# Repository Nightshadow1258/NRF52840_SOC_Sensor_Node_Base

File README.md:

# NRF52840 SOC Sensor Node Base Board

# Version
release Version will be tracked by branches.
Each Version that is/will be produced will branch of main.
Main will always be the most recent version.

## V2.00
- Base Board for the [NRF52840_SOC](https://github.com/Nightshadow1258/NRF52840_SOC)
- changed connector to one with additional retention tabs to increase stability.

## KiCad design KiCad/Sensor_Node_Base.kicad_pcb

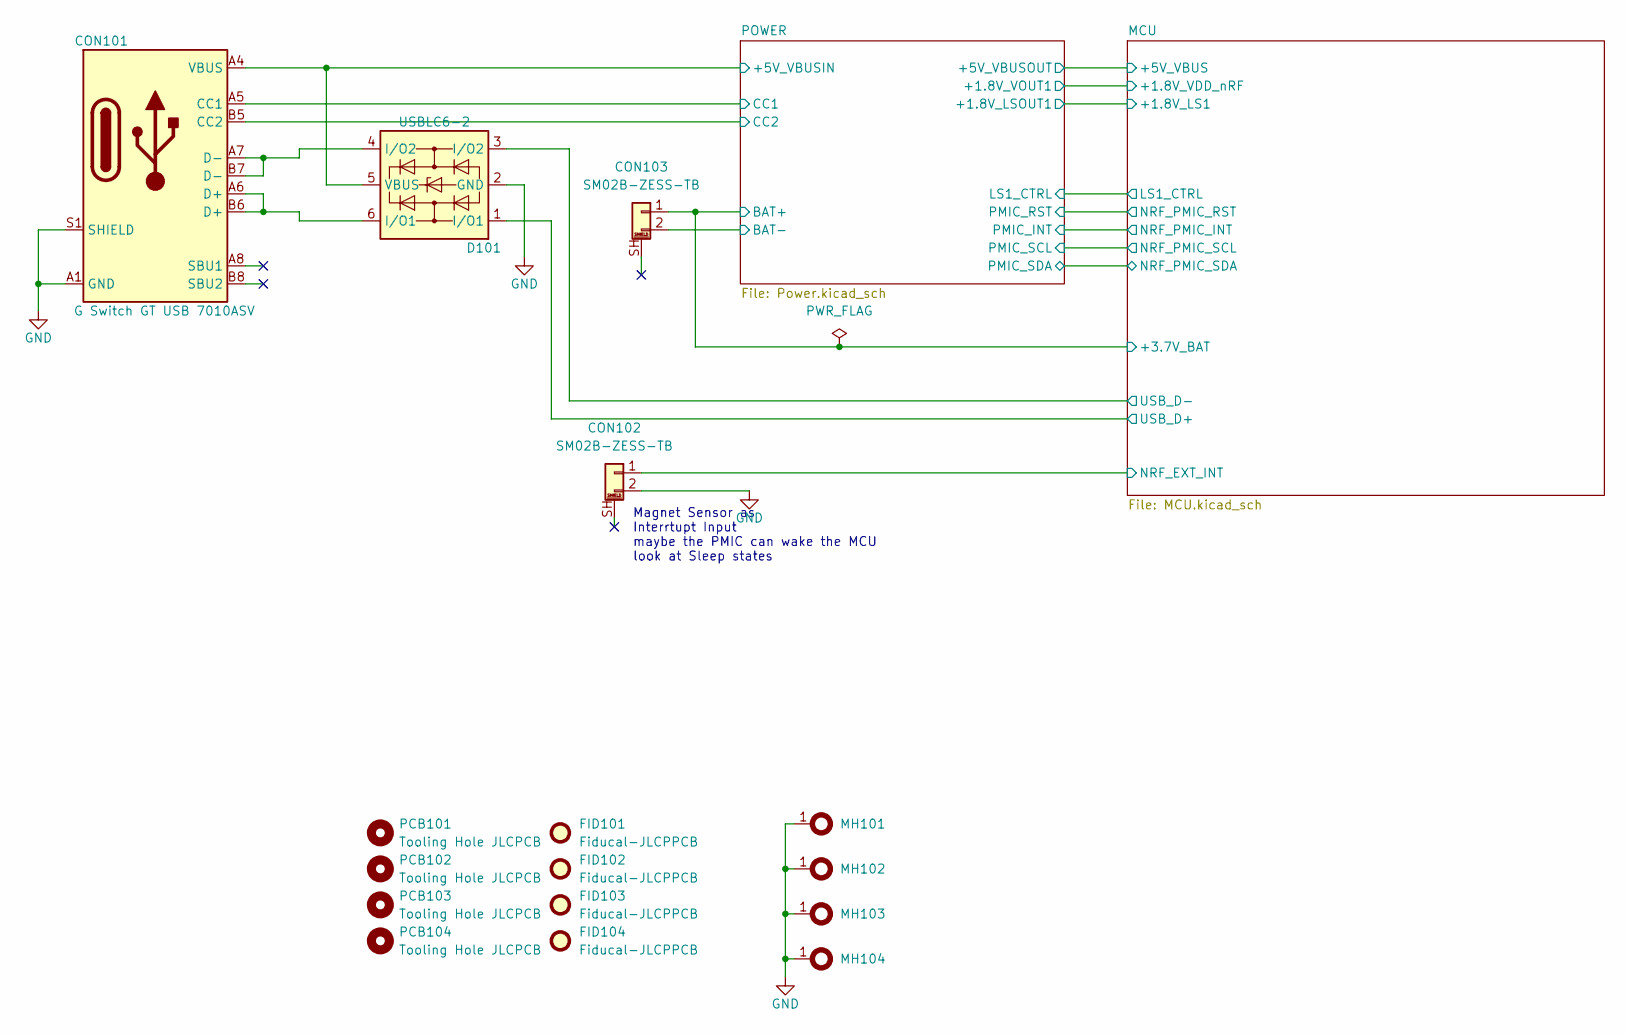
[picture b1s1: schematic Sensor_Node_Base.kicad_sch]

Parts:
CON101: G Switch GT USB 7010ASV; CON-GEN-USB_C-16P; LCSC Part # C2988369
CON102, CON103: SM02B-ZESS-TB; CON-SM02B-ZESS_TB
D101: USBLC6-2; SOT-23-6; LCSC Part # C7519
FID101, FID102, FID103, FID104: Fiducal-JLCPPCB; PCB-FID-JLCPCB
MH101, MH102, MH103, MH104: MountingHole_2.5mm_Pad_Via
PCB101, PCB102, PCB103, PCB104: Tooling Hole JLCPCB; PCB-NPTH-JLCPCB

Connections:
/MCU/+3.7V_BAT: CON103.1; also elsewhere on the board
/MCU/NRF_EXT_INT: CON102.1; also elsewhere on the board
/MCU/USB_D+: D101.1 (I/O1); also elsewhere on the board
/MCU/USB_D-: D101.3 (I/O2); also elsewhere on the board
/POWER/+5V_VBUSIN: CON101.A4 (VBUS), CON101.A9 (VBUS), CON101.B4 (VBUS), CON101.B9 (VBUS), D101.5 (VBUS); also elsewhere on the board
/POWER/BAT-: CON103.2; also elsewhere on the board
/POWER/CC1: CON101.A5 (CC1); also elsewhere on the board
/POWER/CC2: CON101.B5 (CC2); also elsewhere on the board
GND: CON101.A1 (GND), CON101.A12 (GND), CON101.B1 (GND), CON101.B12 (GND), CON101.S1 (SHIELD), CON102.2, D101.2 (GND), MH101.1, MH102.1, MH103.1, MH104.1; also elsewhere on the board
unnamed: CON101.A6 (D+), CON101.B6 (D+), D101.6 (I/O1)
unnamed: CON101.A7 (D-), CON101.B7 (D-), D101.4 (I/O2)

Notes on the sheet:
Magnet Sensor as Interrtupt Input maybe the PMIC can wake the MCU look at Sleep states

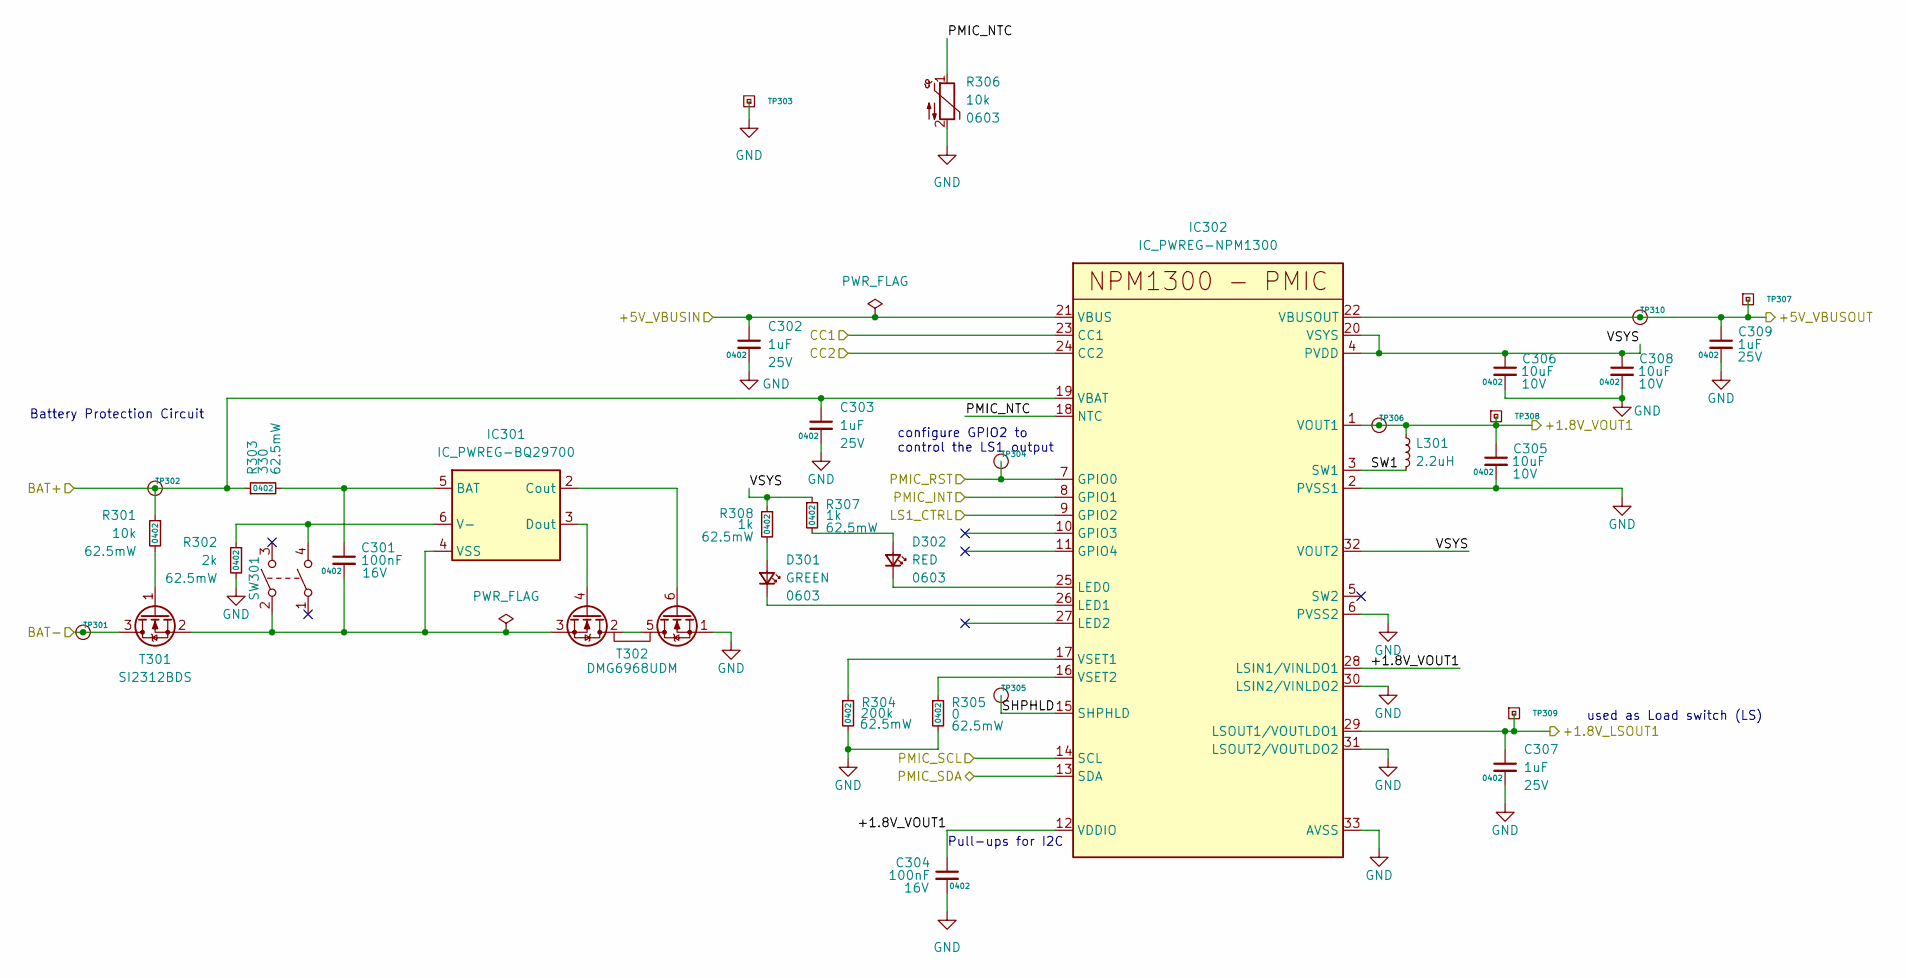
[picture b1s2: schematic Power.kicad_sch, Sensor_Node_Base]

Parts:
C301, C304: 100nF; C_0402_1005Metric; Voltage 16V; LCSC Part # C1525
C302, C303, C307, C309: 1uF; C_0402_1005Metric; Voltage 25V; LCSC Part # C52923
C305, C306, C308: 10uF; C_0603_1608Metric; Voltage 10V; LCSC Part # C96446
D301: GREEN; D_0603_1608Metric; LCSC Part # C84267
D302: RED; D_0603_1608Metric; LCSC Part # C2286
IC301: IC_PWREG-BQ29700; WSON-6_1.5x1.5mm_P0.5mm; LCSC Part # C183096
IC302: IC_PWREG-NPM1300; QFN-32-1EP_5x5mm_P0.5mm_EP3.6x3.6mm_ThermalVias
L301: 2.2uH; L_0806; LCSC Part # C2838367
R301: 10k; R_0402_1005Metric; Power Rating 62.5mW; LCSC Part # C25744
R302: 2k; R_0402_1005Metric; Power Rating 62.5mW; LCSC Part # C4109
R303: 330; R_0402_1005Metric; Power Rating 62.5mW; LCSC Part # C25104
R304: 200k; R_0402_1005Metric; Power Rating 62.5mW; LCSC Part # C25764
R305: 0; R_0402_1005Metric; Power Rating 62.5mW; LCSC Part # C17168
R306: 10k; R_0603_1608Metric; LCSC Part # C142556
R307, R308: 1k; R_0402_1005Metric; Power Rating 62.5mW; LCSC Part # C11702
SW301: SW-GEN-TS-1187A; SW-PUSH-DPST-XKS-TS-1187A; LCSC Part # C318884
T301: SI2312BDS; SOT-23; LCSC Part # C351405
T302: DMG6968UDM; SOT-23-6; LCSC Part # C2762931
TP301, TP302, TP304, TP305, TP306, TP310: TP; TP_Pad_D0.9mm
TP303, TP307, TP308, TP309: Testpoint-BASE; TP_THT_D0.8mm

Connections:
/MCU/+1.8V_LS1: C307.1, IC302.29 (LSOUT1/VOUTLDO1), TP309.1; also elsewhere on the board
/MCU/+1.8V_VDD_nRF: C304.1, C305.1, IC302.1 (VOUT1), IC302.12 (VDDIO), IC302.28 (LSIN1/VINLDO1), L301.1, TP306.1, TP308.1; also elsewhere on the board
/MCU/+3.7V_BAT: C303.1, IC302.19 (VBAT), R301.1, R303.1, TP302.1; also elsewhere on the board
/MCU/+5V_VBUS: C309.1, IC302.22 (VBUSOUT), TP307.1, TP310.1; also elsewhere on the board
/MCU/LS1_CTRL: IC302.9 (GPIO2); also elsewhere on the board
/MCU/NRF_PMIC_INT: IC302.8 (GPIO1); also elsewhere on the board
/MCU/NRF_PMIC_RST: IC302.7 (GPIO0), TP304.1; also elsewhere on the board
/MCU/NRF_PMIC_SCL: IC302.14 (SCL); also elsewhere on the board
/MCU/NRF_PMIC_SDA: IC302.13 (SDA); also elsewhere on the board
/POWER/+5V_VBUSIN: C302.1, IC302.21 (VBUS); also elsewhere on the board
/POWER/BAT-: T301.3 (D), TP301.1; also elsewhere on the board
/POWER/CC1: IC302.23 (CC1); also elsewhere on the board
/POWER/CC2: IC302.24 (CC2); also elsewhere on the board
/POWER/PMIC_NTC: IC302.18 (NTC), R306.1
/POWER/SHPHLD: IC302.15 (SHPHLD), TP305.1
/POWER/SW1: IC302.3 (SW1), L301.2
/POWER/VSYS: C306.1, C308.1, IC302.4 (PVDD), IC302.20 (VSYS), IC302.32 (VOUT2), R307.1, R308.1
GND: C302.2, C303.2, C304.2, C305.2, C306.2, C307.2, C308.2, C309.2, IC302.2 (PVSS1), IC302.6 (PVSS2), IC302.30 (LSIN2/VINLDO2), IC302.31 (LSOUT2/VOUTLDO2), IC302.33 (AVSS), R302.2, R304.2, R305.2, R306.2, T302.1 (S1), TP303.1; also elsewhere on the board
unnamed: D301.2 (A), R308.2
unnamed: D301.1 (K), IC302.26 (LED1)
unnamed: D302.2 (A), R307.2
unnamed: D302.1 (K), IC302.25 (LED0)
unnamed: C301.1, IC301.5 (BAT), R303.2
unnamed: IC301.2 (Cout), T302.6 (G1)
unnamed: IC301.3 (Dout), T302.4 (G2)
unnamed: IC301.6 (V-), R302.1, SW301.4
unnamed: C301.2, IC301.4 (VSS), SW301.2 (3), T301.2 (S), T302.3 (S2)
unnamed: IC302.17 (VSET1), R304.1
unnamed: IC302.16 (VSET2), R305.1
unnamed: R301.2, T301.1 (G)
unnamed: T302.2 (D1/D2), T302.5 (D1/D2)

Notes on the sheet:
Battery Protection Circuit
used as Load switch (LS)
configure GPIO2 to control the LS1 output
Pull-ups for I2C

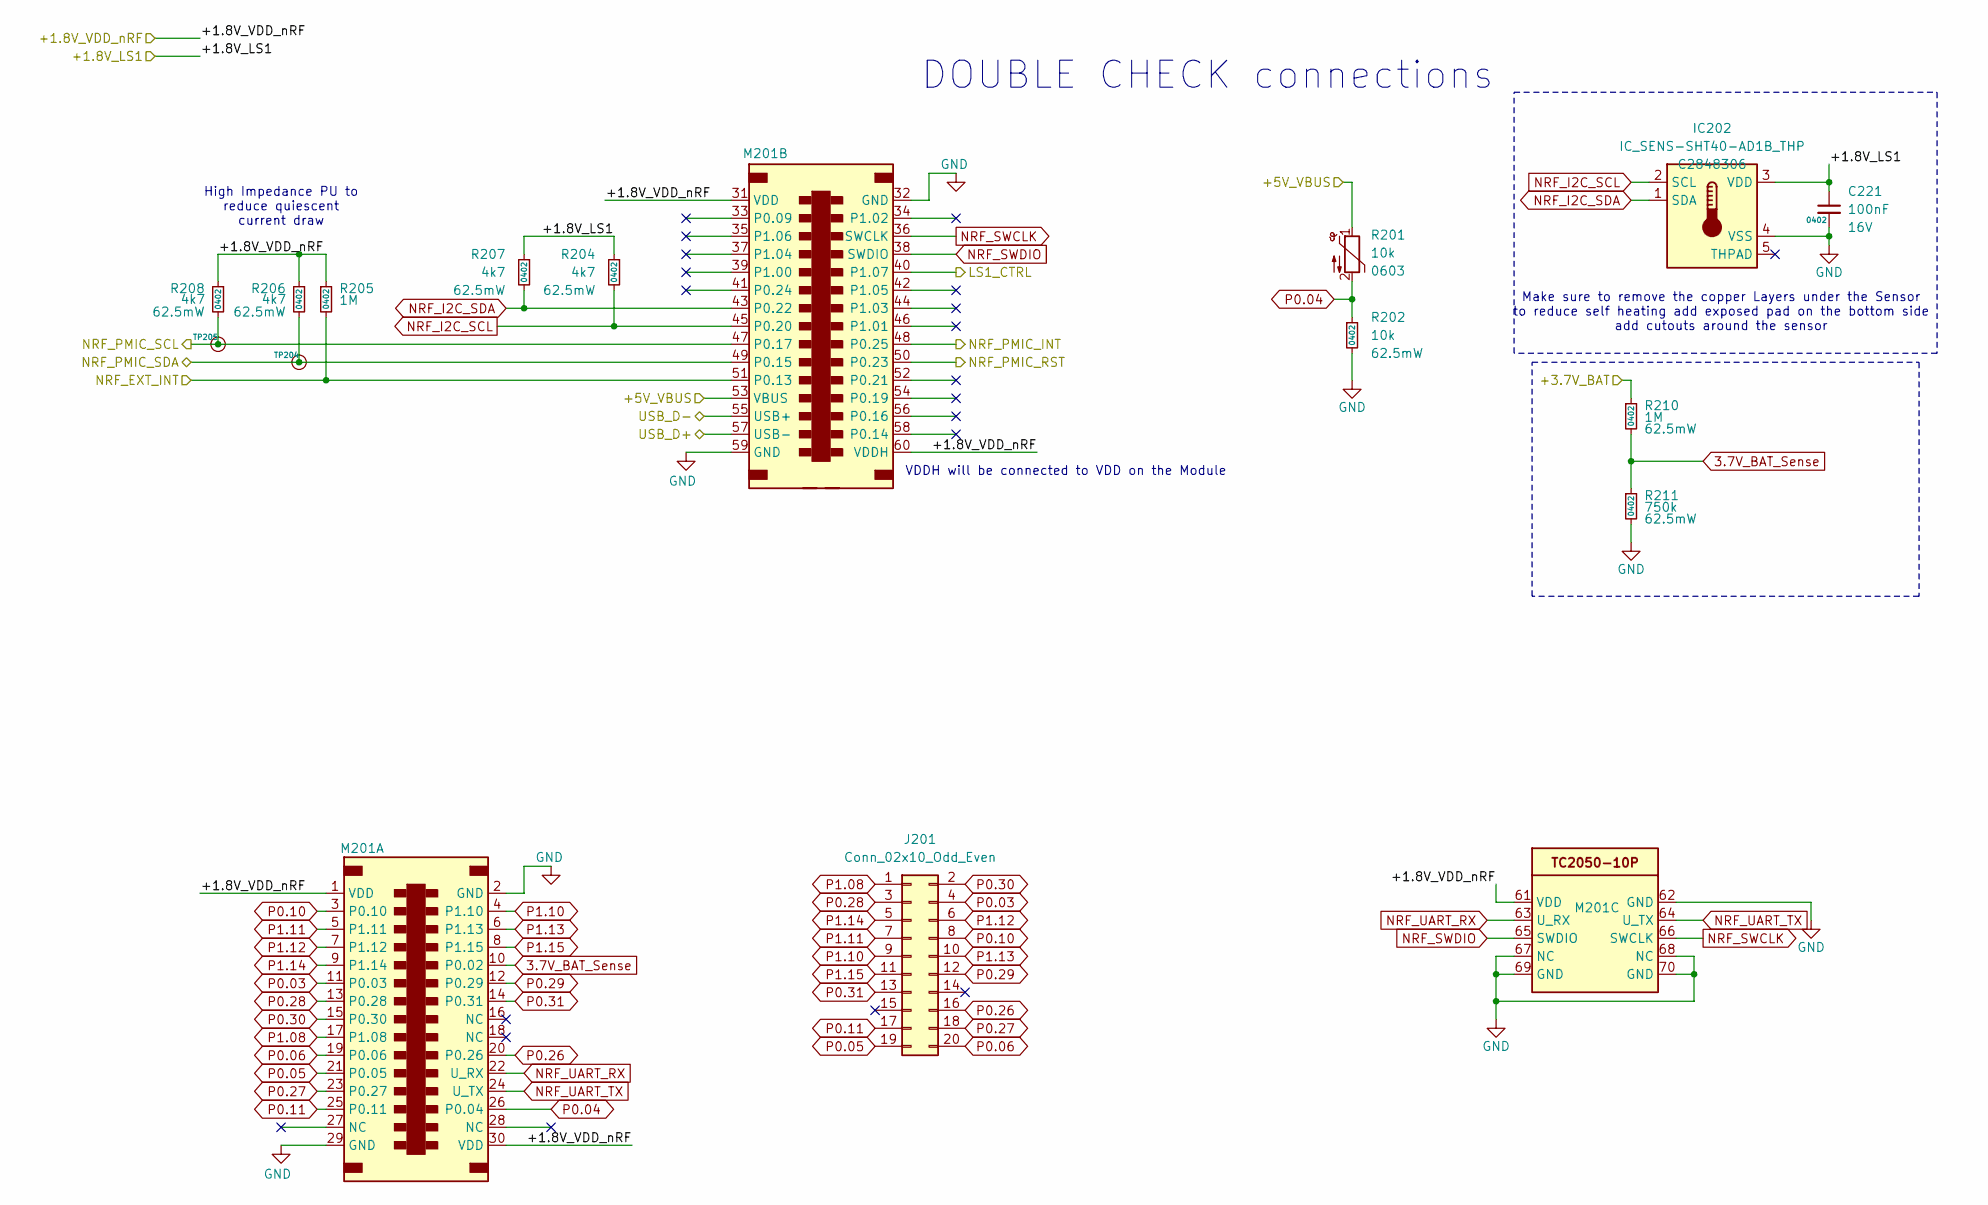
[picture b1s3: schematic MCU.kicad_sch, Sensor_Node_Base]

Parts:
C221: 100nF; C_0402_1005Metric; Voltage 16V; LCSC Part # C1525
IC202: IC_SENS-SHT40-AD1B_THP; DNF-1.5x1.5_H0.54-SHT40-AD1B_THPAD; LCSC Part # C2848306
J201: Conn_02x10_Odd_Even; PinHeader_2x10_P2.54mm_Vertical
M201: M-NRF52840
R201: 10k; R_0603_1608Metric; LCSC Part # C142556
R202: 10k; R_0402_1005Metric; Power Rating 62.5mW; LCSC Part # C25744
R204, R206, R207, R208: 4k7; R_0402_1005Metric; Power Rating 62.5mW; LCSC Part # C25900
R205, R210: 1M; R_0402_1005Metric; Power Rating 62.5mW; LCSC Part # C138033
R211: 750k; R_0402_1005Metric; Power Rating 62.5mW; LCSC Part # C137937
TP204, TP205: TP; TP_Pad_D0.9mm

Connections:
3.7V_BAT_Sense: M201.10 (P0.02), R210.2, R211.1
/MCU/+1.8V_LS1: C221.1, IC202.3 (VDD), R204.1, R207.1; also elsewhere on the board
/MCU/+1.8V_VDD_nRF: M201.1 (VDD), M201.30 (VDD), M201.31 (VDD), M201.60 (VDDH), M201.61 (VDD), R205.1, R206.1, R208.1; also elsewhere on the board
/MCU/+3.7V_BAT: R210.1; also elsewhere on the board
/MCU/+5V_VBUS: M201.53 (VBUS), R201.1; also elsewhere on the board
/MCU/LS1_CTRL: M201.40 (P1.07); also elsewhere on the board
/MCU/NRF_EXT_INT: M201.51 (P0.13), R205.2; also elsewhere on the board
/MCU/NRF_PMIC_INT: M201.48 (P0.25); also elsewhere on the board
/MCU/NRF_PMIC_RST: M201.50 (P0.23); also elsewhere on the board
/MCU/NRF_PMIC_SCL: M201.47 (P0.17), R208.2, TP205.1; also elsewhere on the board
/MCU/NRF_PMIC_SDA: M201.49 (P0.15), R206.2, TP204.1; also elsewhere on the board
/MCU/USB_D+: M201.57 (USB-); also elsewhere on the board
/MCU/USB_D-: M201.55 (USB+); also elsewhere on the board
GND: C221.2, IC202.4 (VSS), M201.2 (GND), M201.29 (GND), M201.32 (GND), M201.59 (GND), M201.62 (GND), M201.67 (NC), M201.68 (NC), M201.69 (GND), M201.70 (GND), R202.2, R211.2; also elsewhere on the board
NRF_I2C_SCL: IC202.2 (SCL), M201.45 (P0.20), R204.2
NRF_I2C_SDA: IC202.1 (SDA), M201.43 (P0.22), R207.2
NRF_SWCLK: M201.36 (SWCLK), M201.66 (SWCLK)
NRF_SWDIO: M201.38 (SWDIO), M201.65 (SWDIO)
NRF_UART_RX: M201.22 (U_RX), M201.63 (U_RX)
NRF_UART_TX: M201.24 (U_TX), M201.64 (U_TX)
P0.03: J201.4, M201.11 (P0.03)
P0.04: M201.26 (P0.04), R201.2, R202.1
P0.05: J201.19, M201.21 (P0.05)
P0.06: J201.20, M201.19 (P0.06)
P0.10: J201.8, M201.3 (P0.10)
P0.11: J201.17, M201.25 (P0.11)
P0.26: J201.16, M201.20 (P0.26)
P0.27: J201.18, M201.23 (P0.27)
P0.28: J201.3, M201.13 (P0.28)
P0.29: J201.12, M201.12 (P0.29)
P0.30: J201.2, M201.15 (P0.30)
P0.31: J201.13, M201.14 (P0.31)
P1.08: J201.1, M201.17 (P1.08)
P1.10: J201.9, M201.4 (P1.10)
P1.11: J201.7, M201.5 (P1.11)
P1.12: J201.6, M201.7 (P1.12)
P1.13: J201.10, M201.6 (P1.13)
P1.14: J201.5, M201.9 (P1.14)
P1.15: J201.11, M201.8 (P1.15)

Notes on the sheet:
VDDH will be connected to VDD on the Module
High Impedance PU to reduce quiescent current draw
DOUBLE CHECK connections
Make sure to remove the copper Layers under the Sensor to reduce self heating add exposed pad on the bottom side add cutouts around the sensor

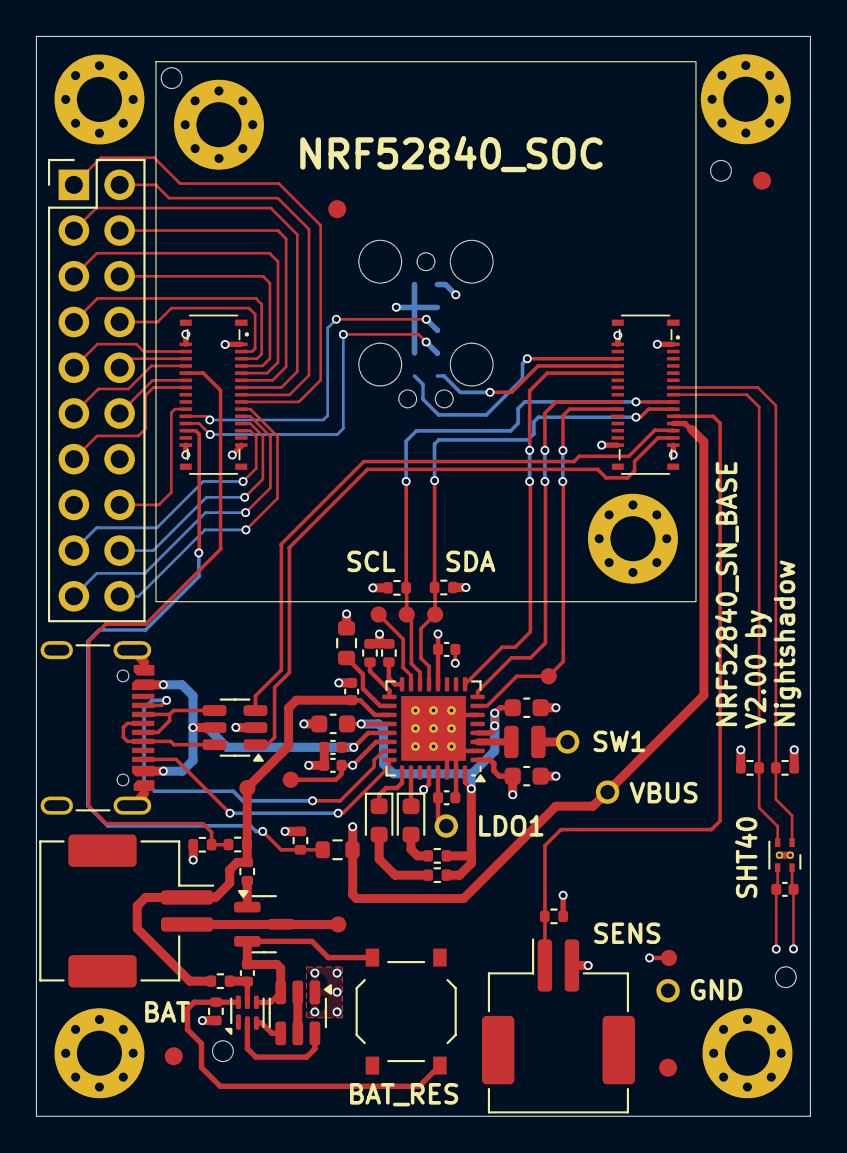
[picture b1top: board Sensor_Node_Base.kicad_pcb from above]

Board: 4 copper layers, 43.0 x 60.0 mm, 66 parts (0 on the bottom side), 62 nets.

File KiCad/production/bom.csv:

Designator,Footprint,Quantity,Value,LCSC Part #
"C221, C301, C304",0402,3,100nF,C1525
"C302, C303, C307, C309",0402,4,1uF,C52923
"C305, C306, C308",0603,3,10uF,C96446
CON101,CON-GEN-USB_C-16P,1,G Switch GT USB 7010ASV,C2988369
"CON102, CON103",CON-SM02B-ZESS_TB,2,SM02B-ZESS-TB,
D101,SOT-23-6,1,USBLC6-2,C7519
D301,0603,1,GREEN,C84267
D302,0603,1,RED,C2286
"FID101, FID102, FID103, FID104",PCB-FID-JLCPCB,4,Fiducal-JLCPPCB,
IC202,DNF-1.5x1.5_H0.54-SHT40-AD1B_THPAD,1,IC_SENS-SHT40-AD1B_THP,C2848306
IC301,WSON-6_1.5x1.5mm_P0.5mm,1,IC_PWREG-BQ29700,C183096
IC302,QFN-32-1EP_5x5mm_P0.5mm_EP3.6x3.6mm_ThermalVias,1,IC_PWREG-NPM1300,
J201,PinHeader_2x10_P2.54mm_Vertical,1,Conn_02x10_Odd_Even,
L301,L_0806,1,2.2uH,C2838367
M201,M-NRF52840,1,~,
"MH101, MH102, MH103, MH104",MountingHole_2.5mm_Pad_Via,4,~,
"PCB101, PCB102, PCB103, PCB104",PCB-NPTH-JLCPCB,4,Tooling Hole JLCPCB,
"R201, R306",0603,2,10k,C142556
"R202, R301",0402,2,10k,C25744
"R204, R206, R207, R208",0402,4,4k7,C25900
"R205, R210",0402,2,1M,C138033
R211,0402,1,750k,C137937
R302,0402,1,2k,C4109
R303,0402,1,330,C25104
R304,0402,1,200k,C25764
R305,0402,1,0,C17168
"R307, R308",0402,2,1k,C11702
SW301,SW-PUSH-DPST-XKS-TS-1187A,1,SW-GEN-TS-1187A,C318884
T301,SOT-23,1,SI2312BDS, C351405 
T302,SOT-23-6,1,DMG6968UDM, C2762931
"TP204, TP205, TP301, TP302, TP304, TP305, TP306, TP310",TP_Pad_D0.9mm,8,TP,
"TP303, TP307, TP308, TP309",TP_THT_D0.8mm,4,Testpoint-BASE,

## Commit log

2025-09-20 V1.00 commit
2025-09-20 rename to generic name
2025-09-26 added button to reset the battery proteciton.
